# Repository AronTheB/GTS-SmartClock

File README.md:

# GTS-Smart Clock

<br><br/>

### DEMO VIDEO: https://youtu.be/dEGiFh21TzU

For some reason I always need to run to the bus stop so I can catch the bus, so instead of trying to leave earlier I designed the GTS Smart Clock which can tell me when to leave so I reach it without running and waiting.

For my first non guided Hardware project i made a Smart Clock that can tell me the time, but it also connects to the public transport API and tells me when i my next bus going and also when will i get to my destination if i leave at that moment. Other features will be added in the future

### The project uses a Xiao ESP32 C3, a OLED SSD1306 Screen, and a MxCherry switch with a keycap.

The clock is pretty simple to use. It has a single button which changes the current mode to the next one. The smart clock can be built by downloading the Gerber PCB files and buying them from a PCB printing company like JLCPCB or PCBWAY. You also need to buy the correct components which are linked in the BOM section, and 3d print the case or design a new one. After everything arrives solder everything to the board and upload the firmware to the ESP32. After that just put everything in the case like in the CAD model and connect it to power via a c-type cable. You can close the case by mainly screwing it in the screwhole with a 2mm x 5mm screw, but you could make it work with saller or a bit larger one (If your 3d printer cant print the icons on the top just remove them from the model and print it without them)

### You need to also set up a config.h file in the included folder. (you might have to rewrite the api part of the code if you are using a different api)

#define WIFI_SSID     "WIFINAME"

#define WIFI_PASSWORD "WIFIPASSPORT"

#define BKK_API_KEY   "PUBLICTRANSPORTAPIKEY"

#define BKK_STOP_ID    "BUSSTOPID"

#define BUS_ROUTE_SHORT_NAME "BUSNAME"

#define BUS_DIRECTION_HEADSIGN "BUSDESTINATION"

In the pcb the pins for the oled screen are reveresd so you need to use wires to wire them in instead of a header pin

## KIKAD
This is the Schematic:

<br></br>

This is the PCB layout and wiring:

<br></br>
## FUSION
This is the 3D Model of the case:

## Build

## BOM

| Name               | Link        | Price  | Quantity | Need To Buy? |
|--------------------|------------|--------|----------|--------------|
| XIAO ESP32      | [LINK](https://www.seeedstudio.com/Seeed-XIAO-ESP32C3-p-5431.html) | $5.13  | 1 | Yes |
| SSD1306            | [LINK](https://www.aliexpress.com/item/1005006141235306.html?spm=a2g0o.productlist.0.0.1ec2tPXFtPXFrn&mp=1) | $1.00  | 1 | Yes |
| Cherry MX Switch   | [LINK](https://www.aliexpress.com/item/1005008586371182.html?spm=a2g0o.productlist.main.5.1ec2tPXFtPXFrn&algo_pvid=3f7b64de-8767-4574-abf2-40f9073028dd&pdp_ext_f=%7B%22order%22%3A%22130%22%2C%22spu_best_type%22%3A%22price%22%2C%22eval%22%3A%221%22%2C%22fromPage%22%3A%22search%22%7D&utparam-url=scene%3Asearch%7Cquery_from%3A%7Cx_object_id%3A1005008586371182%7C_p_origin_prod%3A) | $2.09  | 1 | No  |
| Cherry MX Keycaps  | [LINK](https://www.aliexpress.com/item/1005002906017844.html?spm=a2g0o.productlist.main.2.7587d75duLmAxW&algo_pvid=7f1486d7-8f33-438b-a090-75c0d12eb0bc&pdp_ext_f=%7B%22order%22%3A%22578%22%2C%22eval%22%3A%221%22%2C%22fromPage%22%3A%22search%22%7D&utparam-url=scene%3Asearch%7Cquery_from%3A%7Cx_object_id%3A1005002906017844%7C_p_origin_prod%3A) | $1.00  | 1 | No  |
| 3D Case            | Printing Legion     | Free + Shipping | 1 | Yes |
| PCB                | JLCPCB     | ≈ $5.00 | 1 | Yes |

**Total Cost:** $14.22

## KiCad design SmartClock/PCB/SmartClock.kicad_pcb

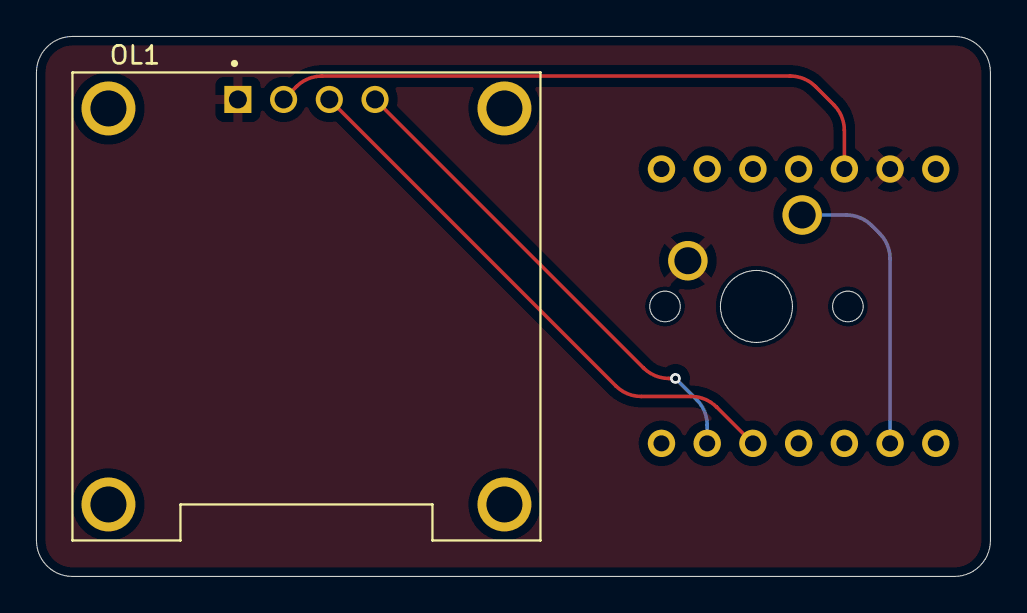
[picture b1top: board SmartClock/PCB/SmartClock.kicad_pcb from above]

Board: 2 copper layers, 53.0 x 30.0 mm, 3 parts (1 on the bottom side), 5 nets.

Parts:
OL1: OLED; MODULE_DM-OLED096-636
SW1: SW_Push; SW_Cherry_MX_1.00u_PCB
U2: XIAO-ESP32-C3-DIP

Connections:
GND: OL1.1 (GND), SW1.2, U2.13 (GND)
unnamed: OL1.3 (SCL), U2.5 (GPIO6_D4_SDA)
unnamed: OL1.4 (SDA), U2.6 (GPIO7_D5_SCL)
unnamed: OL1.2 (VCC), U2.12 (3V3)
unnamed: SW1.1, U2.2 (GPIO3_A1_D1)

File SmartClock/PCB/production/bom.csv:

Designator,Footprint,Quantity,Value,LCSC Part #
OL1,MODULE_DM-OLED096-636,1,OLED,
SW1,SW_Cherry_MX_1.00u_PCB,1,SW_Push,
U2,XIAO-ESP32-C3-DIP,1,XIAO-ESP32-C3-DIP,

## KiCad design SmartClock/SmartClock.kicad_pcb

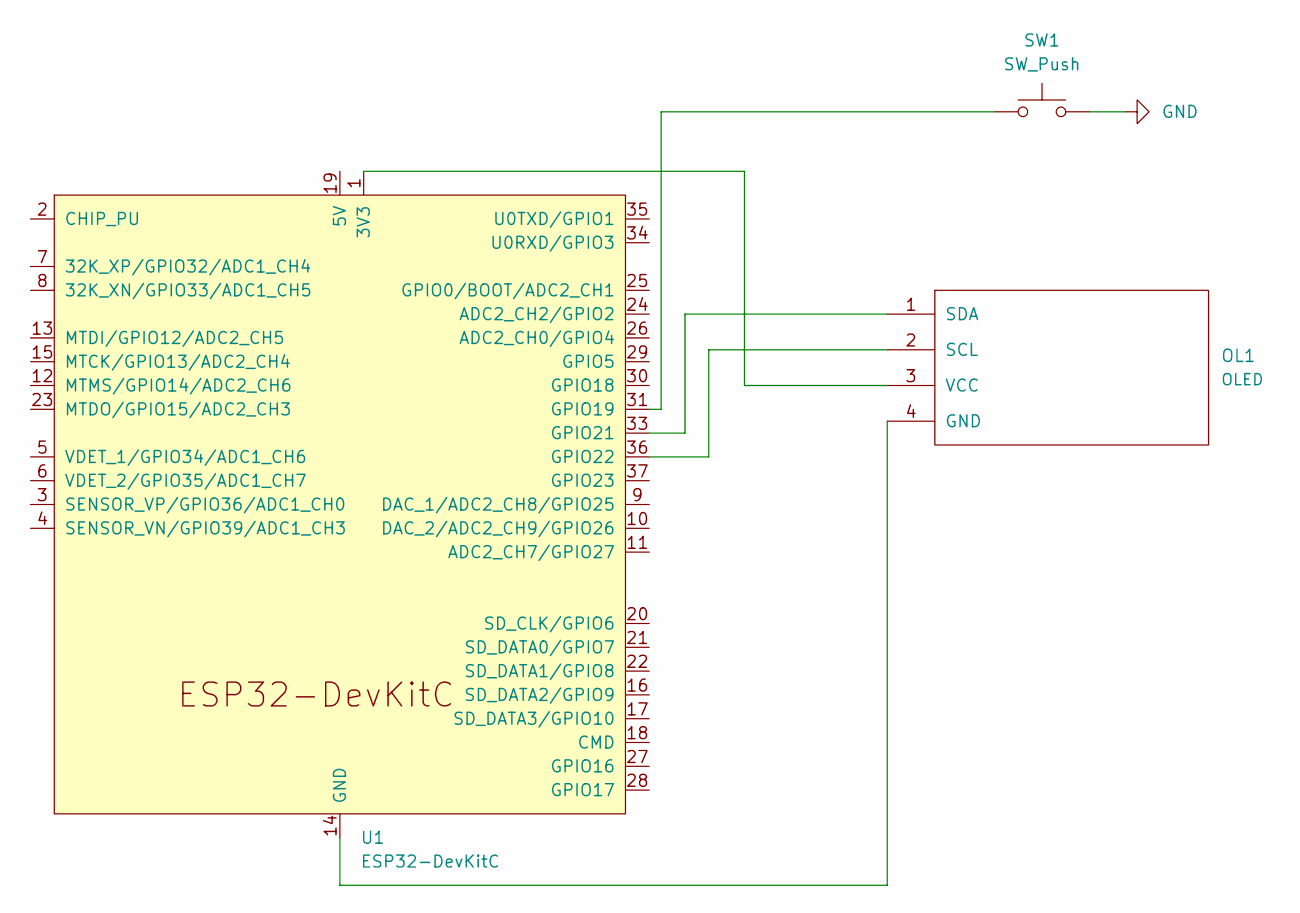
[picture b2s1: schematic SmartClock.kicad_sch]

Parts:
OL1: OLED
SW1: SW_Push; SW_Cherry_MX_1.00u_PCB
U1: ESP32-DevKitC

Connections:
GND: SW1.2
unnamed: OL1.4 (GND), U1.14 (GND), U1.32 (GND), U1.38 (GND)
unnamed: OL1.2 (SCL), U1.36 (GPIO22)
unnamed: OL1.1 (SDA), U1.33 (GPIO21)
unnamed: OL1.3 (VCC), U1.1 (3V3)
unnamed: SW1.1, U1.31 (GPIO19)

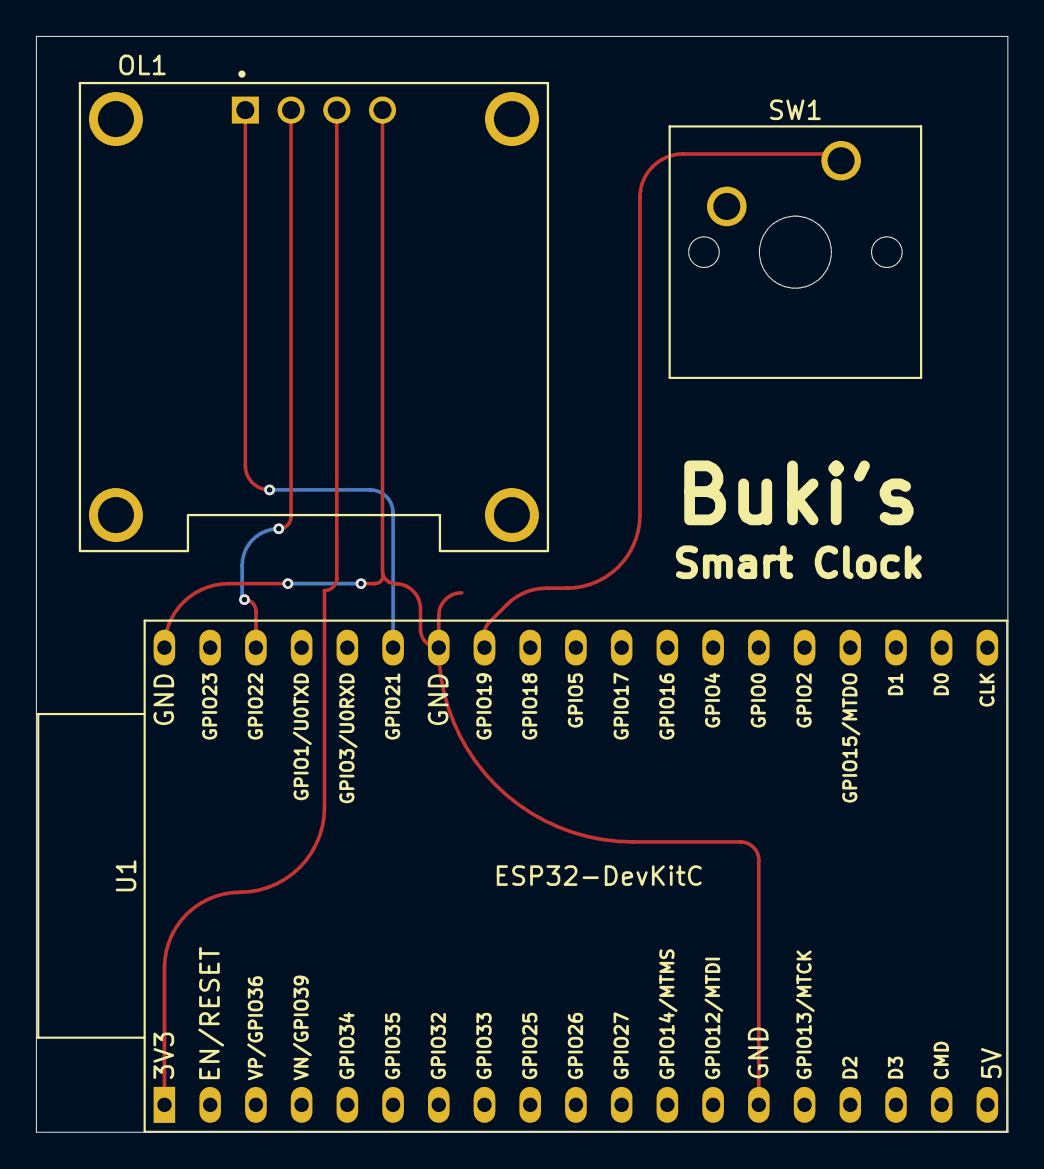
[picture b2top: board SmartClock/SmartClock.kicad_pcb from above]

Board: 2 copper layers, 54.0 x 60.9 mm, 3 parts (0 on the bottom side), 5 nets.

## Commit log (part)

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2026-04-05 added stuff
2026-04-05 Added Fusion files
2026-04-05 Rename project to GTFTS-SmartClock and expand README
    Updated project name and added detailed project description with images.
2026-04-05 added framework
2026-04-13 Add Bill of Materials section to READMEbom
2026-04-13 bomfix
2026-04-14 changed pcb
2026-04-18 Update image in README for 3D model
2026-04-20 Revise README with updated project details
    Updated project description and details about components.
2026-04-20 Update ESP32 DevKitC link in BOM
2026-04-20 Remove BOM section header from README
    Removed the BOM section header from the README.
2026-04-20 3d models + remmove
2026-04-20 added zine
2026-04-20 Update README with build instructions for Smart Clock
    Added instructions for building the Smart Clock with PCB files and components.
2026-04-20 Clarify usage instructions for the smart clock
    Updated description of the smart clock project for clarity.
2026-04-20 added step files
2026-04-20 Update README with 3D printing instructions
    Added note about 3D printing icons on the clock case.
2026-04-22 fixed issues
2026-04-22 added gerber files
2026-04-22 added button functionality
2026-05-23 production
